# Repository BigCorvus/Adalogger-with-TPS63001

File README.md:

# Adalogger-with-TPS63001
The SAMD21-based feather adalogger with a different voltage regulator. It uses a TPS63001 synchronous buck boost chip to be able to use LiFePO4 batteries and still have a steady 3.3v. Another advantage is that more capacity can be squeezed out of LiPos, still maintaining a stable 3.3V rail.

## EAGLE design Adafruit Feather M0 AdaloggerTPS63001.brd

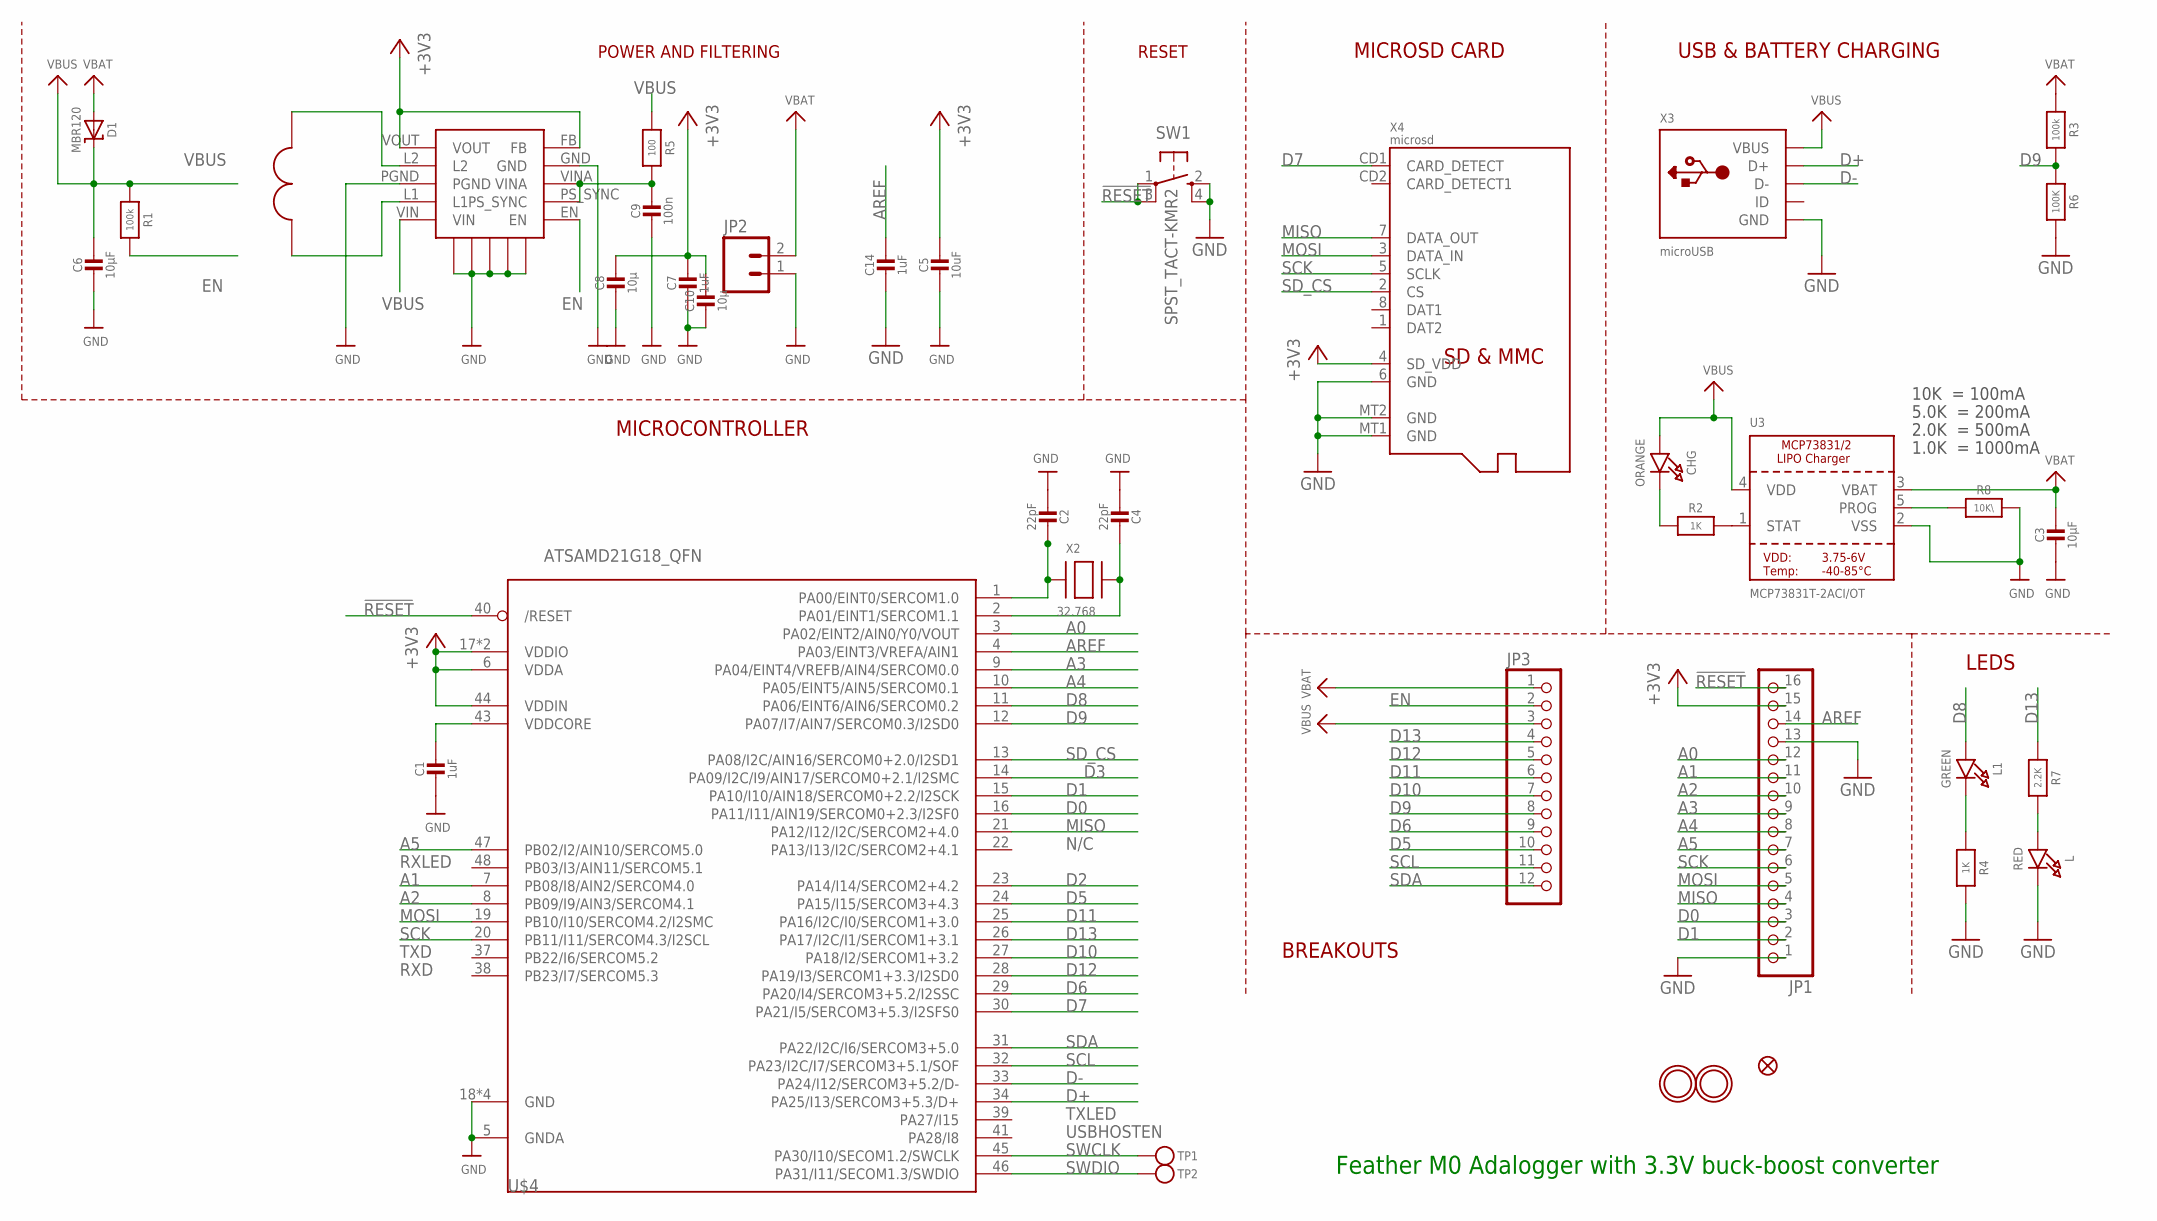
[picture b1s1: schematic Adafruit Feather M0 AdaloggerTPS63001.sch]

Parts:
C1, C7, C14: 1uF; 0603-NO
C2, C4: 22pF; 0603-NO
C3, C6: 10µF; 0805-NO
C5: 10uF; 0805-NO
C8, C10: 10µ; 0603-NO
C9: 100n; 0603-NO
CHG: ORANGE; CHIPLED_0805_NOOUTLINE
D1: MBR120; SOD-123
JP1: HEADER-1X16ROUND; 1X16_ROUND
JP2: M02PTH; 1X02
JP3: HEADER-1X12; 1X12_ROUND
L: RED; CHIPLED_0805_NOOUTLINE
L1: GREEN; CHIPLED_0805_NOOUTLINE
R1, R3: 100k; 0603-NO
R2, R4: 1K; 0603-NO
R5: 100; 0603-NO
R6: 100K; 0603-NO
R7: 2.2K; 0603-NO
R8: 10K\; 0603-NO
SW1: SPST_TACT-KMR2; KMR2
TP1, TP2: TESTPOINTROUND1.5MM; TESTPOINT_ROUND_1.5MM
U3: MCP73831T-2ACI/OT; SOT23-5
U$4: ATSAMD21G18_QFN; TQFN48_7MM
U$12: TPS63001
U$15: VLF4012A
U$31, U$32: MOUNTINGHOLE2.5; MOUNTINGHOLE_2.5_PLATED
U$35: FIDUCIAL""; FIDUCIAL_1MM
X2: 32.768; XTAL3215
X3: microUSB; 4UCONN_20329_V2
X4: microsd; MICROSD

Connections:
!RESET: JP1.16, SW1.1, SW1.3 (P1), U$4.40 (/RESET)
+3V3: C5.1, C7.1, C8.1, C10.1, JP1.15, U$4.6 (VDDA), U$4.17 (VDDIO), U$4.36 (VDDIO), U$4.44 (VDDIN), U$12.FB, U$12.VOUT, X4.4 (SD_VDD)
A0: JP1.12, U$4.3 (PA02/EINT2/AIN0/Y0/VOUT)
A1: JP1.11, U$4.7 (PB08/I8/AIN2/SERCOM4.0)
A2: JP1.10, U$4.8 (PB09/I9/AIN3/SERCOM4.1)
A3: JP1.9, U$4.9 (PA04/EINT4/VREFB/AIN4/SERCOM0.0)
A4: JP1.8, U$4.10 (PA05/EINT5/AIN5/SERCOM0.1)
A5: JP1.7, U$4.47 (PB02/I2/AIN10/SERCOM5.0)
AREF: C14.1, JP1.14, U$4.4 (PA03/EINT3/VREFA/AIN1)
D0: JP1.3, U$4.16 (PA11/I11/AIN19/SERCOM0+2.3/I2SF0)
D1: JP1.2, U$4.15 (PA10/I10/AIN18/SERCOM0+2.2/I2SCK)
D2: U$4.23 (PA14/I14/SERCOM2+4.2)
D3: U$4.14 (PA09/I2C/I9/AIN17/SERCOM0+2.1/I2SMC)
D5: JP3.10, U$4.24 (PA15/I15/SERCOM3+4.3)
D6: JP3.9, U$4.29 (PA20/I4/SERCOM3+5.2/I2SSC)
D7: U$4.30 (PA21/I5/SERCOM3+5.3/I2SFS0), X4.CD1 (CARD_DETECT)
D8: L1.A, U$4.11 (PA06/EINT6/AIN6/SERCOM0.2)
D9: JP3.8, R3.2, R6.1, U$4.12 (PA07/I7/AIN7/SERCOM0.3/I2SD0)
D10: JP3.7, U$4.27 (PA18/I2/SERCOM1+3.2)
D11: JP3.6, U$4.25 (PA16/I2C/I0/SERCOM1+3.0)
D12: JP3.5, U$4.28 (PA19/I3/SERCOM1+3.3/I2SD0)
D13: JP3.4, R7.1, U$4.26 (PA17/I2C/I1/SERCOM1+3.1)
D+: U$4.34 (PA25/I13/SERCOM3+5.3/D+), X3.D+
D-: U$4.33 (PA24/I12/SERCOM3+5.2/D-), X3.D-
EN: JP3.2, R1.2, U$12.EN
GND: C1.2, C2.2, C3.2, C4.2, C5.2, C6.2, C7.2, C8.2, C9.2, C10.2, C14.2, JP1.1, JP1.13, JP2.1, L.C, R4.2, R6.2, R8.2, SW1.2 (S), SW1.4 (S1), U3.2 (VSS), U$4.5 (GNDA), U$4.18 (GND), U$4.35 (GND), U$4.42 (GND), U$4.THERMAL (GND), U$12.GND, U$12.GNDP1, U$12.GNDP2, U$12.GNDP3, U$12.GNDP4, U$12.GNDP5, U$12.PGND, X3.BASE@1 (GND), X3.BASE@2 (GND), X3.GND, X3.SPRT@1 (GND), X3.SPRT@2 (GND), X3.SPRT@3 (GND), X3.SPRT@4 (GND), X4.6 (GND), X4.MT1 (GND), X4.MT2 (GND)
MISO: JP1.4, U$4.21 (PA12/I12/I2C/SERCOM2+4.0), X4.7 (DATA_OUT)
MOSI: JP1.5, U$4.19 (PB10/I10/SERCOM4.2/I2SMC), X4.3 (DATA_IN)
unnamed: CHG.C, R2.1
unnamed: L.A, R7.2
unnamed: R2.2, U3.1 (STAT)
unnamed: R8.1, U3.5 (PROG)
unnamed: C2.1, U$4.1 (PA00/EINT0/SERCOM1.0), X2.P$1
unnamed: L1.C, R4.1
unnamed: C4.1, U$4.2 (PA01/EINT1/SERCOM1.1), X2.P$2
unnamed: U$12.L1, U$15.P$1
unnamed: U$12.L2, U$15.P$2
SCK: JP1.6, U$4.20 (PB11/I11/SERCOM4.3/I2SCL), X4.5 (SCLK)
SCL: JP3.11, U$4.32 (PA23/I2C/I7/SERCOM3+5.1/SOF)
SDA: JP3.12, U$4.31 (PA22/I2C/I6/SERCOM3+5.0)
SD_CS: U$4.13 (PA08/I2C/AIN16/SERCOM0+2.0/I2SD1), X4.2 (CS)
SWCLK: TP1.P$1, U$4.45 (PA30/I10/SECOM1.2/SWCLK)
SWDIO: TP2.P$1, U$4.46 (PA31/I11/SECOM1.3/SWDIO)
VBAT: C3.1, D1.A, JP2.2, JP3.1, R3.1, U3.3 (VBAT)
VBUS: C6.1, CHG.A, D1.C, JP3.3, R1.1, R5.1, U3.4 (VDD), U$12.VIN, X3.VBUS
VDDCORE: C1.1, U$4.43 (VDDCORE)
VINA_ETC: C9.1, R5.2, U$12.PS_SYNC, U$12.VINA

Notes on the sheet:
POWER AND FILTERING
RESET
10K = 100mA
5.0K = 200mA
2.0K = 500mA
1.0K = 1000mA
N/C
TXLED
USBHOSTEN
RXLED
TXD
RXD
USB & BATTERY CHARGING
MICROSD CARD
BREAKOUTS
LEDS
MICROCONTROLLER
Feather M0 Adalogger with 3.3V buck-boost converter

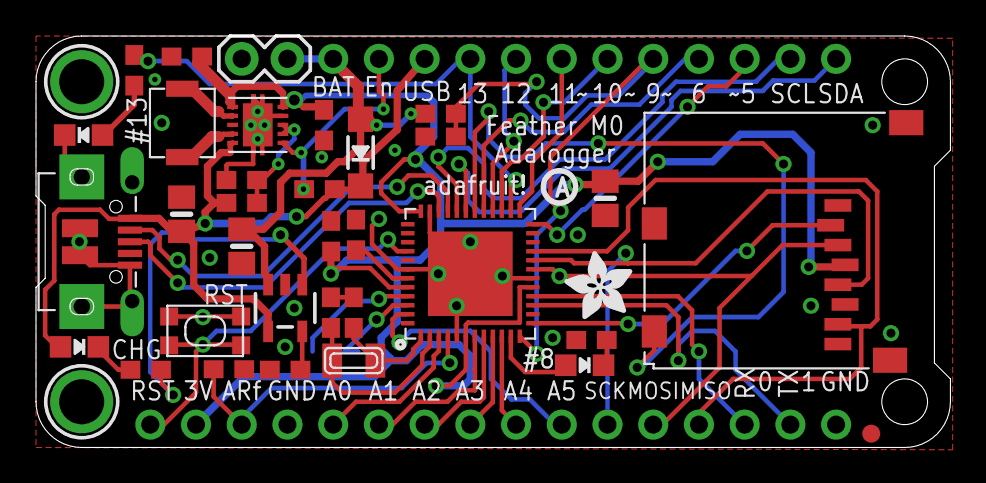
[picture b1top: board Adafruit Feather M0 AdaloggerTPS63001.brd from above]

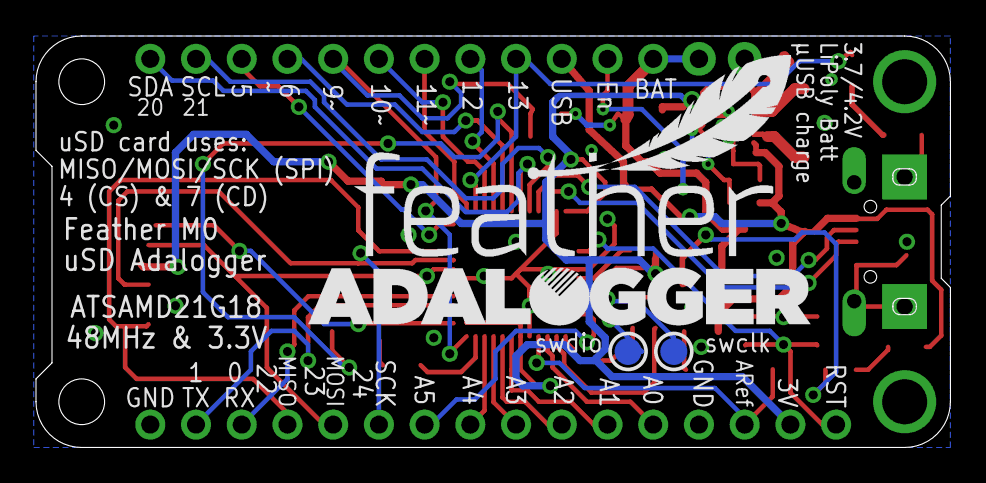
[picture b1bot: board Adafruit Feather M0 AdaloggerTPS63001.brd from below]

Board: 2 copper layers, 50.8 x 22.9 mm, 43 parts (4 on the bottom side), 45 nets.

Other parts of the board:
U$7: ADAFRUIT_3.5MM
U$9: PCBFEAT-REV-040
U$13: FEATHERLOGO
U$14: ADALOGGER_LOGO

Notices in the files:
parts and their libraries:
microbuilder: This work is placed in the public domain, and may be freely used for commercial and non-commercial work with the following conditions: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
SparkFun-Connectors: Licensing: Creative Commons ShareAlike 4.0 International - https://creativecommons.org/licenses/by-sa/4.0
